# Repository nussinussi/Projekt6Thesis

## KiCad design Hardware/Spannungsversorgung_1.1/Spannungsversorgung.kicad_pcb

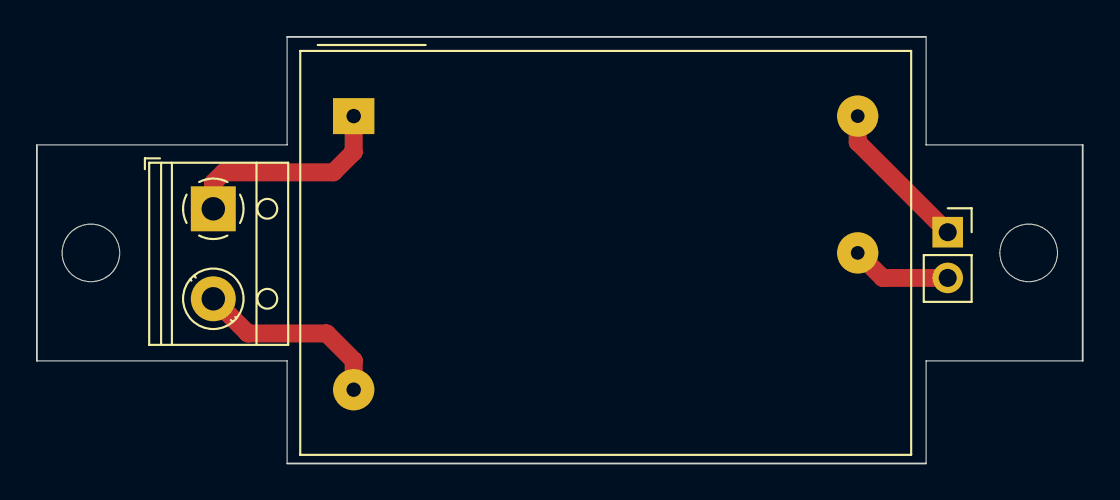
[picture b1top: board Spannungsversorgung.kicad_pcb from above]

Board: 2 copper layers, 58.1 x 23.7 mm, 5 parts (0 on the bottom side), 4 nets.

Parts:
H1, H2: MountingHole; MountingHole_3.2mm_M3_ISO14580
J1: Screw_Terminal_01x02; TerminalBlock_RND_205-00012_1x02_P5.00mm_Horizontal
J2: Conn_01x02_Male; PinSocket_1x02_P2.54mm_Vertical
PS1: IRM-02-5; Converter_ACDC_MeanWell_IRM-02-xx_THT

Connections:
unnamed: J1.1, PS1.1
unnamed: J1.2, PS1.2
unnamed: J2.1, PS1.3
unnamed: J2.2, PS1.4

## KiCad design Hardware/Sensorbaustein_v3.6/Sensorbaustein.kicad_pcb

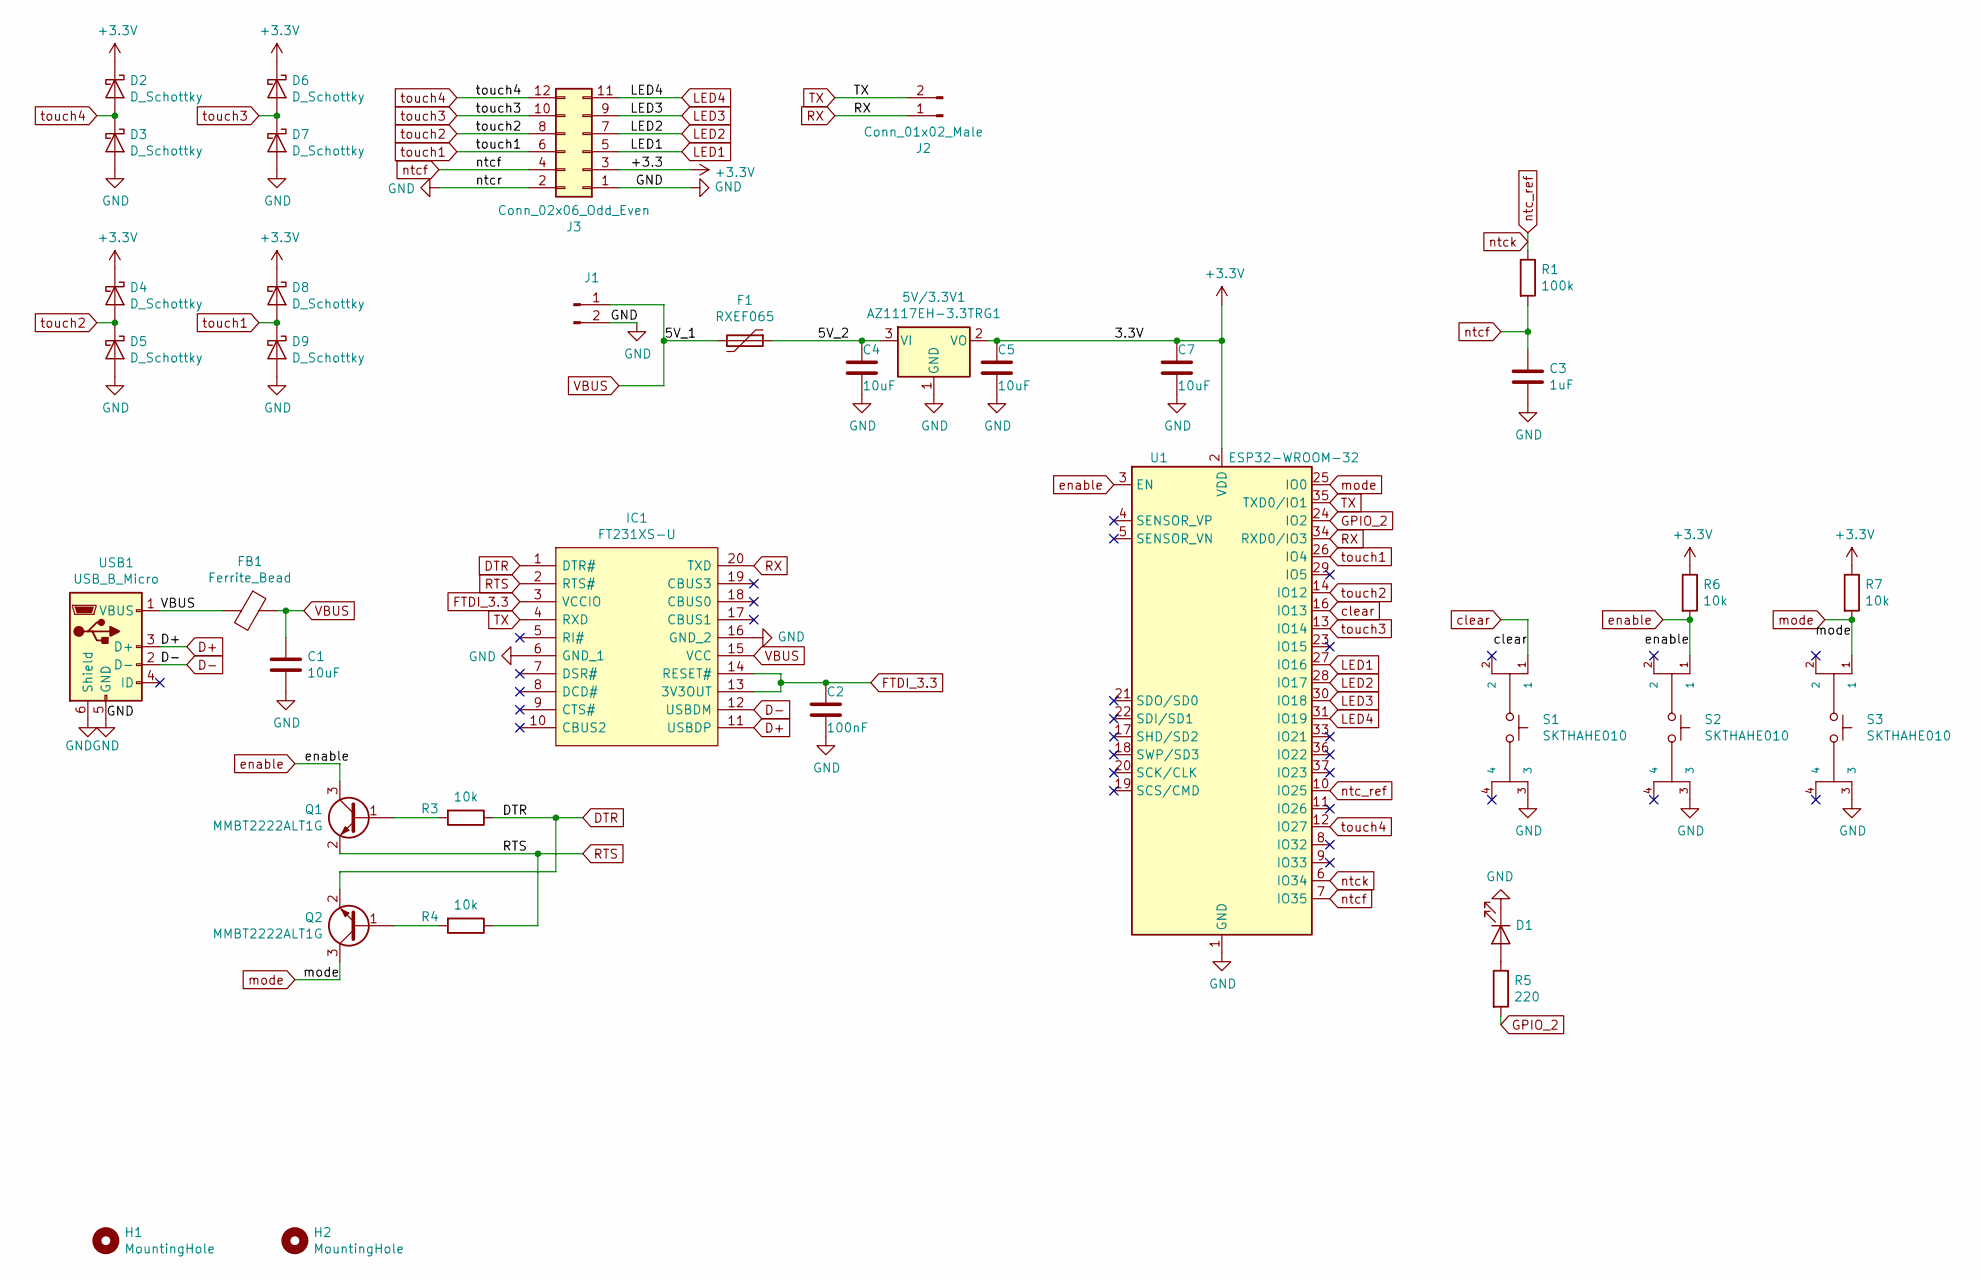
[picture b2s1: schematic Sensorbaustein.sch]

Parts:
5V/3.3V1: AZ1117EH-3.3TRG1; SOT-223-3_TabPin2
C1, C4, C5, C7: 10uF; C_0603_1608Metric_Pad1.05x0.95mm_HandSolder
C2: 100nF; C_0603_1608Metric_Pad1.05x0.95mm_HandSolder
C3: 1uF; C_0603_1608Metric_Pad1.05x0.95mm_HandSolder
D1: 150060BS55040; LED_0603_1608Metric_Pad1.05x0.95mm_HandSolder
D2, D3, D4, D5, D6, D7, D8, D9: D_Schottky; D_SOT-23_ANK
F1: RXEF065; RXEF050
FB1: Ferrite_Bead; R_0603_1608Metric_Pad1.05x0.95mm_HandSolder
H1, H2: MountingHole; MountingHole_3.2mm_M3_ISO14580
IC1: FT231XS-U; SOP64P599X175-20N; Manufacturer_Part_Number FT231XS-U; Mouser Part Number 895-FT231XS-U
J1, J2: Conn_01x02_Male; PinHeader_1x02_P2.54mm_Vertical
J3: Conn_02x06_Odd_Even; PinSocket_2x06_P2.54mm_Vertical
Q1, Q2: MMBT2222ALT1G; SOT-23
R1: 100k; R_0603_1608Metric_Pad1.05x0.95mm_HandSolder
R3, R4, R6, R7: 10k; R_0603_1608Metric_Pad1.05x0.95mm_HandSolder
R5: 220; R_0603_1608Metric_Pad1.05x0.95mm_HandSolder
S1, S2, S3: SKTHAHE010; SW_SKTHAHE010
U1: ESP32-WROOM-32
USB1: USB_B_Micro; USB_Micro-B_Wuerth_629105150521

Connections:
+3V3: 5V/3.3V1.2 (VO), C5.1, C7.1, D2.1 (K), D4.1 (K), D6.1 (K), D8.1 (K), J3.3, R6.1, R7.1, U1.2 (VDD)
/5V_2: 5V/3.3V1.3 (VI), C4.1, F1.1
D+: IC1.11 (USBDP), USB1.3 (D+)
D-: IC1.12 (USBDM), USB1.2 (D-)
DTR: IC1.1 (DTR#), Q2.2 (E), R3.1
FTDI_3.3: C2.1, IC1.3 (VCCIO), IC1.13 (3V3OUT), IC1.14 (RESET#)
GND: 5V/3.3V1.1 (GND), C1.2, C2.2, C3.2, C4.2, C5.2, C7.2, D1.1 (K), D3.2 (A), D5.2 (A), D7.2 (A), D9.2 (A), IC1.6 (GND_1), IC1.16 (GND_2), J1.2, J3.1, J3.2, S1.3, S2.3, S3.3, U1.1 (GND), U1.15 (GND), U1.38 (GND), USB1.5 (GND), USB1.6 (Shield)
GPIO_2: R5.2, U1.24 (IO2)
LED1: J3.5, U1.27 (IO16)
LED2: J3.7, U1.28 (IO17)
LED3: J3.9, U1.30 (IO18)
LED4: J3.11, U1.31 (IO19)
unnamed: D1.2 (A), R5.1
unnamed: Q1.1 (B), R3.2
unnamed: Q2.1 (B), R4.2
RTS: IC1.2 (RTS#), Q1.2 (E), R4.1
RX: IC1.20 (TXD), J2.1, U1.34 (RXD0/IO3)
TX: IC1.4 (RXD), J2.2, U1.35 (TXD0/IO1)
VBUS: C1.1, F1.2, FB1.1, FB1.2, IC1.15 (VCC), J1.1, USB1.1 (VBUS)
clear: S1.1, U1.16 (IO13)
enable: Q1.3 (C), R6.2, S2.1, U1.3 (EN)
mode: Q2.3 (C), R7.2, S3.1, U1.25 (IO0)
ntc_ref: R1.1, U1.6 (IO34), U1.10 (IO25)
ntcf: C3.1, J3.4, R1.2, U1.7 (IO35)
touch1: D8.2 (A), D9.1 (K), J3.6, U1.26 (IO4)
touch2: D4.2 (A), D5.1 (K), J3.8, U1.14 (IO12)
touch3: D6.2 (A), D7.1 (K), J3.10, U1.13 (IO14)
touch4: D2.2 (A), D3.1 (K), J3.12, U1.12 (IO27)

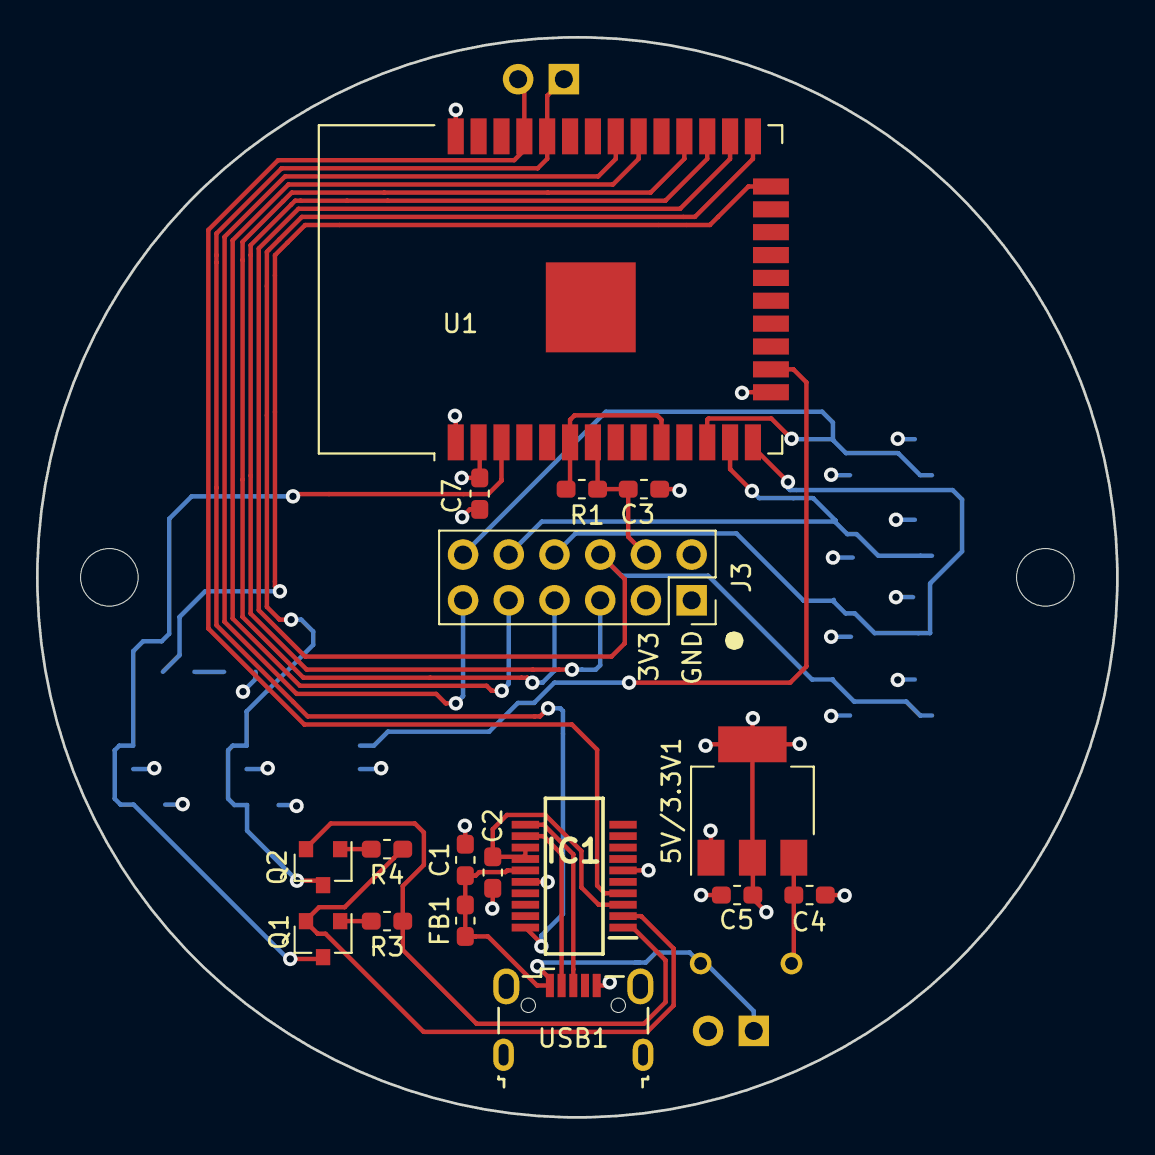
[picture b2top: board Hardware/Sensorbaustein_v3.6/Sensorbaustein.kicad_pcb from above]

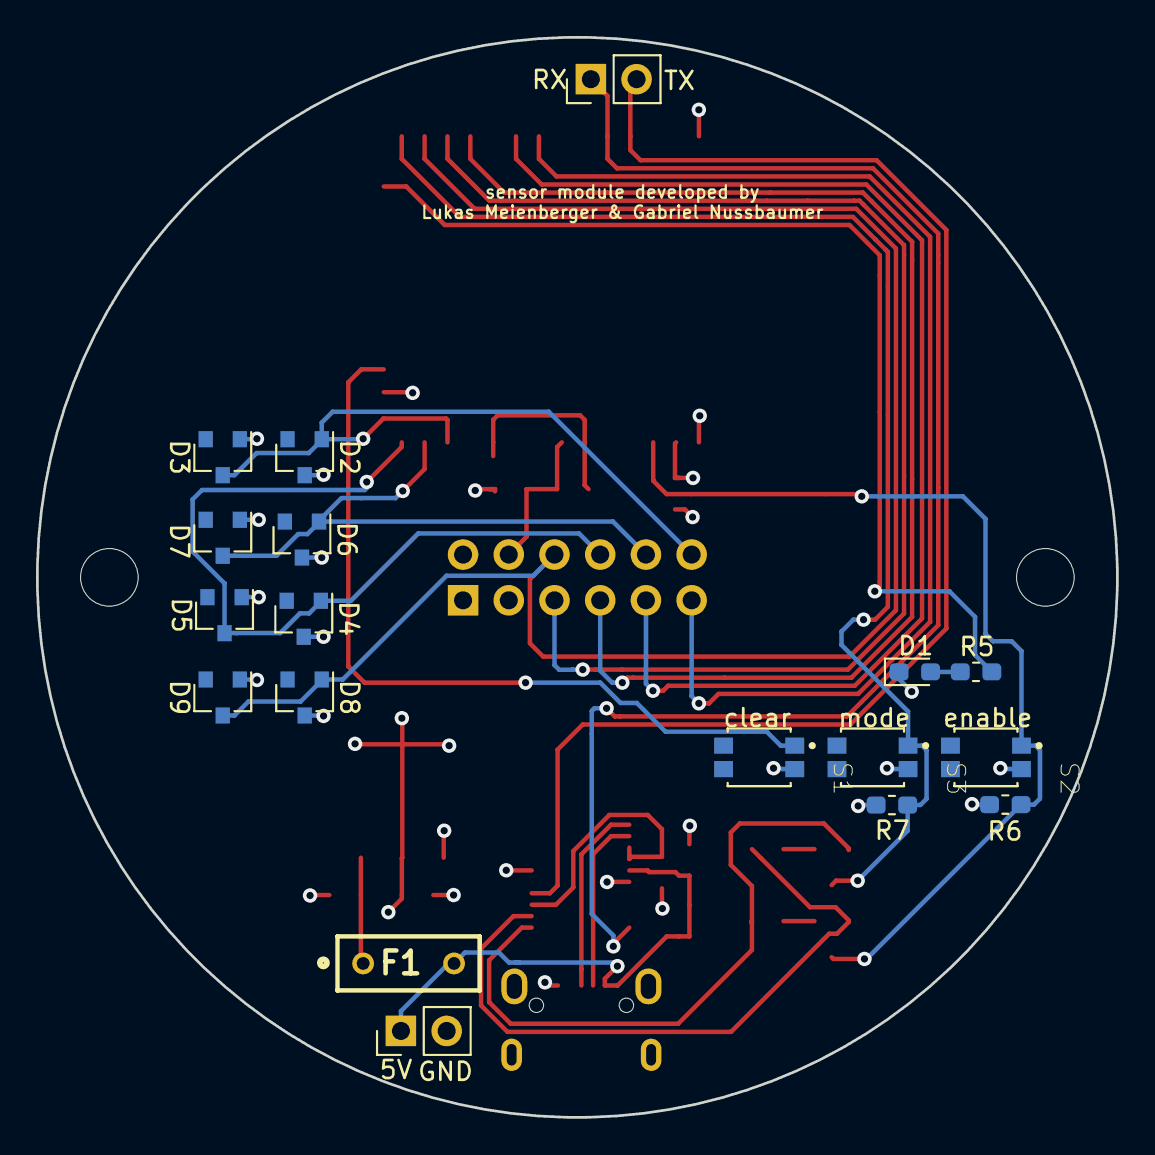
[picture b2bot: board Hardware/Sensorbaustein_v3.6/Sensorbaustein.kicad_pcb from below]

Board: 4 copper layers, 60.0 x 60.0 mm, 37 parts (18 on the bottom side), 28 nets.

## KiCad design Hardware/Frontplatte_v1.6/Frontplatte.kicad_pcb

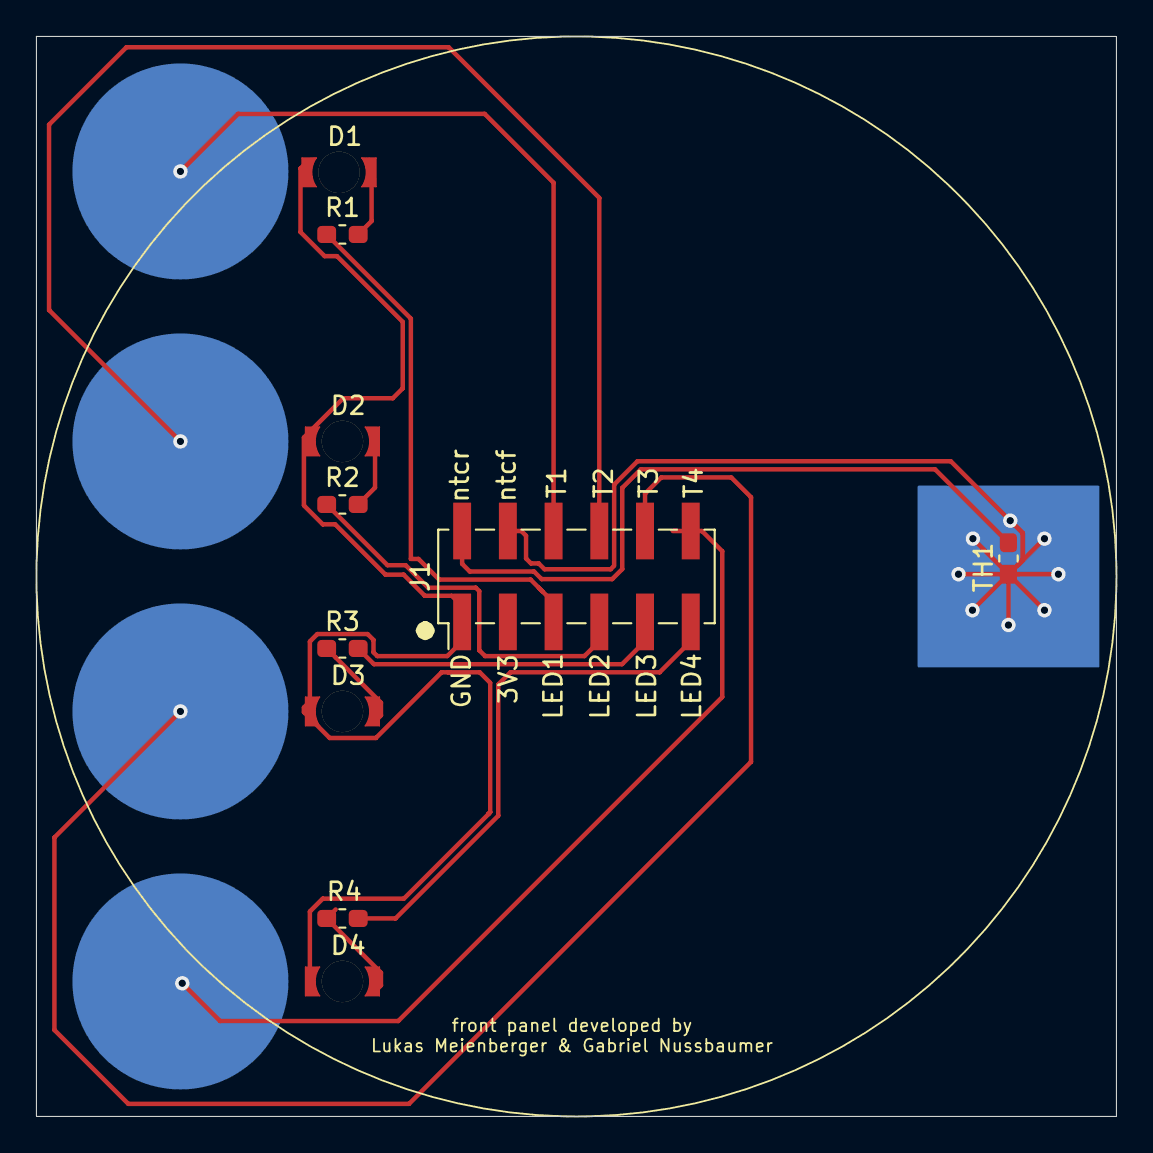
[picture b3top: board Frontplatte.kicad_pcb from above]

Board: 2 copper layers, 60.0 x 60.0 mm, 14 parts (0 on the bottom side), 11 nets.

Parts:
D1, D2, D3, D4: 156120RS75000; reverse_mounted_LED_hole_2.3mm
J1: 61000621121; PinHeader_2x06_P2.54mm_Vertical_SMD
R1, R2, R3, R4: 100; R_0603_1608Metric_Pad1.05x0.95mm_HandSolder
TA1, TA2, TA3, TA4: touch_area_round_12mm; touch_area
TH1: NCU18WF104J60RB; R_0603_1608Metric_Pad1.05x0.95mm_HandSolder

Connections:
GND: D1.1, D2.1, D3.1, D4.1, J1.1
LED1: J1.5, R1.2
LED2: J1.7, R2.2
LED3: J1.9, R3.2
LED4: J1.11, R4.2
unnamed: D1.2, R1.1
unnamed: D2.2, R2.1
unnamed: D3.2, R3.1
unnamed: D4.2, R4.1
ntcf: J1.4, TH1.1
ntcr: J1.2, TH1.2

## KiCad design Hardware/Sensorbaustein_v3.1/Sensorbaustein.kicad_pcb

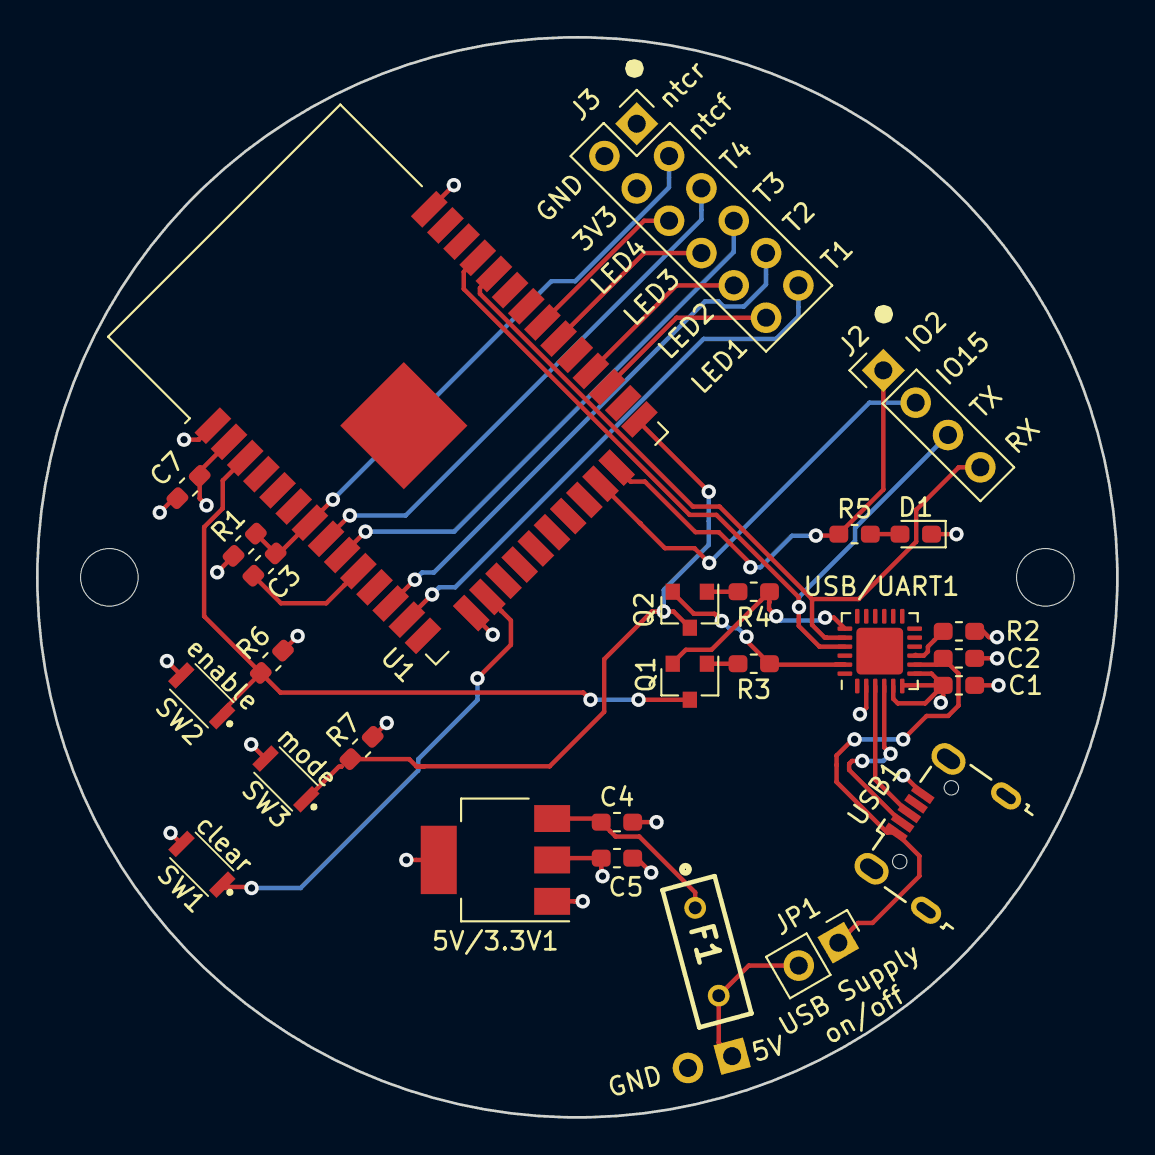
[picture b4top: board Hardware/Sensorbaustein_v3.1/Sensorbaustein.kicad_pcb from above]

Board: 4 copper layers, 60.0 x 60.0 mm, 30 parts (1 on the bottom side), 30 nets.

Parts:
5V/3.3V1: AZ1117EH-3.3TRG1; SOT-223-3_TabPin2
C1: 4.7uF; C_0603_1608Metric_Pad1.05x0.95mm_HandSolder
C2: 100nF; C_0603_1608Metric_Pad1.05x0.95mm_HandSolder
C3: 1uF; C_0603_1608Metric_Pad1.05x0.95mm_HandSolder
C4, C5, C7: 10uF; C_0603_1608Metric_Pad1.05x0.95mm_HandSolder
D1: 150060BS55040; LED_0603_1608Metric_Pad1.05x0.95mm_HandSolder
F1: RXEF065; RXEF050
H1, H2: MountingHole; MountingHole_3.2mm_M3_ISO14580
J1: Conn_01x02_Male; PinHeader_1x02_P2.54mm_Vertical
J2: Conn_01x04_Male; PinHeader_1x04_P2.54mm_Vertical
J3: Conn_02x06_Odd_Even; PinSocket_2x06_P2.54mm_Vertical
JP1: Conn_01x02_Male; PinHeader_1x02_P2.54mm_Vertical
Q1, Q2: MMBT3904; SOT-23
R1: 100k; R_0603_1608Metric_Pad1.05x0.95mm_HandSolder
R2, R3, R4, R6, R7: 10k; R_0603_1608Metric_Pad1.05x0.95mm_HandSolder
R5: 220; R_0603_1608Metric_Pad1.05x0.95mm_HandSolder
SW1, SW2, SW3: TL3780AF100QG; TL3750AF240QG
U1: ESP32-WROOM-32
USB1: USB_B_Micro; USB_Micro-B_Wuerth_629105150521
USB/UART1: CP2104; QFN-24-1EP_4x4mm_P0.5mm_EP2.6x2.6mm

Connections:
+1V1: R1.1, U1.10
+3V3: 5V/3.3V1.2, C1.1, C5.1, C7.1, J3.4, R2.1, R6.1, R7.1, U1.2, USB/UART1.5, USB/UART1.6, USB/UART1.7
/5V_1: F1.2, J1.1, JP1.2
/5V_2: 5V/3.3V1.3, C4.1, F1.1
CHIP_PU: Q1.3, R6.2, SW2.1, U1.3
D+: USB1.3, USB/UART1.3
D-: USB1.2, USB/UART1.4
DTR: Q2.2, R3.1, USB/UART1.23
GND: 5V/3.3V1.1, C1.2, C2.2, C3.2, C4.2, C5.2, C7.2, D1.1, J1.2, J3.1, J3.2, SW1.2, SW2.2, SW3.2, U1.1, U1.15, U1.38, USB1.5, USB1.6, USB/UART1.2
GPIO_0: Q2.3, R7.2, SW3.1, U1.25
GPIO_2: J2.1, R5.2, U1.24
GPIO_15: J2.2, U1.23
LED1: J3.12, U1.27
LED2: J3.10, U1.28
LED3: J3.8, U1.30
LED4: J3.6, U1.31
unnamed: D1.2, R5.1
unnamed: Q1.1, R3.2
unnamed: Q2.1, R4.2
unnamed: R2.2, USB/UART1.9
RTS: Q1.2, R4.1, USB/UART1.19
RXD: J2.4, U1.34, USB/UART1.20
SysReset: SW1.1, U1.16
TXD: J2.3, U1.35, USB/UART1.21
VBUS: C2.1, JP1.1, USB1.1, USB/UART1.8
ntc: C3.1, J3.3, R1.2, U1.7
touch1: J3.11, U1.13
touch2: J3.9, U1.12
touch3: J3.7, U1.9
touch4: J3.5, U1.8

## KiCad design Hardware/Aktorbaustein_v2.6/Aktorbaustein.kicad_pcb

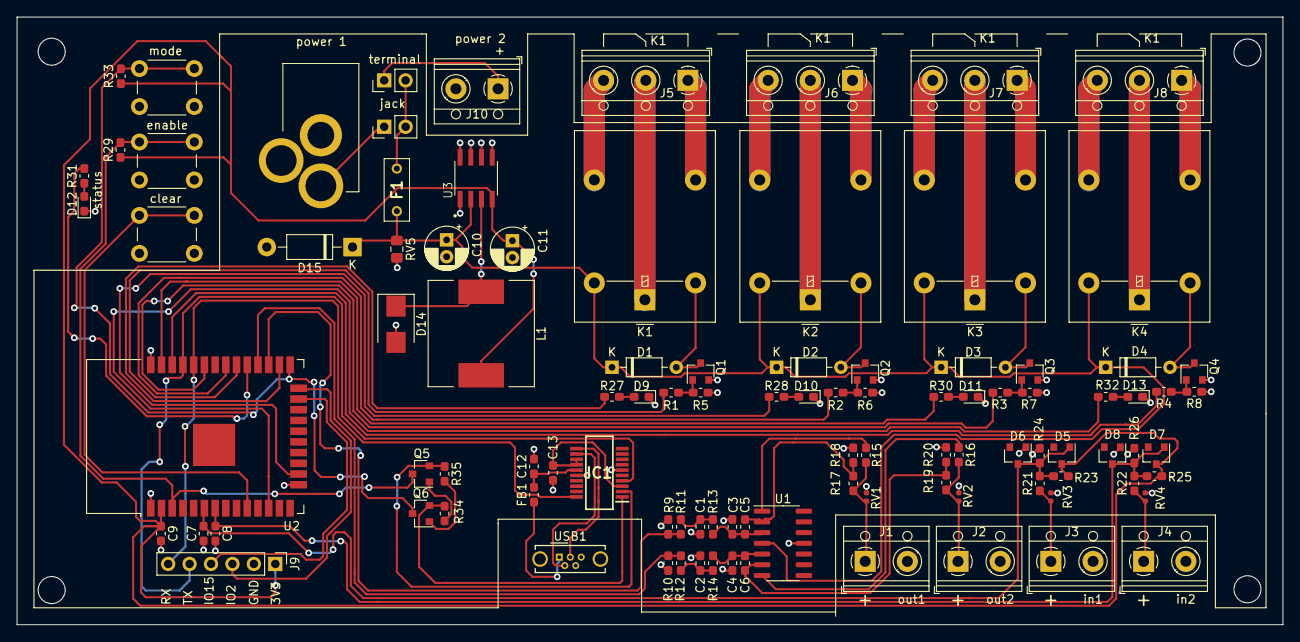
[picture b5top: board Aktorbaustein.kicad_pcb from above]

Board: 2 copper layers, 150.0 x 72.0 mm, 106 parts (0 on the bottom side), 73 nets.

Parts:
C1, C2, C7, C8, C13: 100nF; C_0603_1608Metric_Pad1.05x0.95mm_HandSolder
C3, C4: 10nF; C_0603_1608Metric_Pad1.05x0.95mm_HandSolder
C5, C6: 1nF; C_0603_1608Metric_Pad1.05x0.95mm_HandSolder
C9, C12: 10uF; C_0603_1608Metric_Pad1.05x0.95mm_HandSolder
C10, C11: 15uF; CP_Radial_D5.0mm_P2.00mm
D1, D2, D3, D4: 1N4148; D_DO-35_SOD27_P7.62mm_Horizontal
D5, D6, D7, D8: BAT54; D_SOT-23_ANK
D9, D10, D11, D13: 150060VS55040; LED_0603_1608Metric_Pad1.05x0.95mm_HandSolder
D12: 150060BS55040; LED_0603_1608Metric_Pad1.05x0.95mm_HandSolder
D14: B260; D_SMB
D15: 1N4001G; D_DO-41_SOD81_P10.16mm_Horizontal
F1: RXEF020-AP; RXEF0252
FB1: Ferrite_Bead; R_0603_1608Metric_Pad1.05x0.95mm_HandSolder
H1, H2, H3, H4: MountingHole; MountingHole_3.2mm_M3_ISO7380
IC1: FT231XS-U; SOP64P599X175-20N
J1, J2, J3, J4: TB001-500-02BE; TerminalBlock_RND_205-00012_1x02_P5.00mm_Horizontal
J5, J6, J7, J8: TB002-500-03BE; TerminalBlock_RND_205-00013_1x03_P5.00mm_Horizontal
J9: Conn_01x06_Male; PinHeader_1x06_P2.54mm_Vertical
J10: TB003V-500-P02BE; TerminalBlock_RND_205-00012_1x02_P5.00mm_Horizontal
J11: CON-SOCJ-2155; CONSOCJ2155
JP1, JP2: Jumper; PinHeader_1x02_P2.54mm_Vertical
K1, K2, K3, K4: G5LE-1-VD DC24; Relay_SPDT_Omron-G5LE-1
L1: SRR1260-681K; L_12x12mm_H6mm
Q1, Q2, Q3, Q4: BSS123; SOT-23
Q5, Q6: MMBT3904; SOT-23
R1, R2, R3, R4: 330; R_0603_1608Metric_Pad1.05x0.95mm_HandSolder
R5, R6, R7, R8: 100k; R_0603_1608Metric_Pad1.05x0.95mm_HandSolder
R9, R10, R15, R16, R18, R20, R29, R33, R34, R35: 10k; R_0603_1608Metric_Pad1.05x0.95mm_HandSolder
R11, R12: 3.9k; R_0603_1608Metric_Pad1.05x0.95mm_HandSolder
R13, R14: 39k; R_0603_1608Metric_Pad1.05x0.95mm_HandSolder
R17, R19: 22k; R_0603_1608Metric_Pad1.05x0.95mm_HandSolder
R21, R22: 33k; R_0603_1608Metric_Pad1.05x0.95mm_HandSolder
R23, R25: 120k; R_0603_1608Metric_Pad1.05x0.95mm_HandSolder
R24, R26: 11k; R_0603_1608Metric_Pad1.05x0.95mm_HandSolder
R27, R28, R30, R31, R32: 220; R_0603_1608Metric_Pad1.05x0.95mm_HandSolder
RV1, RV2, RV3, RV4: CG0402MLA-14LG; R_0402_1005Metric
RV5: AVRM2012C330KT801N; R_0805_2012Metric_Pad1.15x1.40mm_HandSolder
SW1, SW2, SW3: SKHHALA010; SW_PUSH_6mm_H4.3mm
U1: LM324A; SOIC-14_3.9x8.7mm_P1.27mm
U2: ESP32-WROOM-32
U3: MIC4680-3.3YM-TR; SOIC127P600X175-8N
USB1: USB_B_Micro; USB_Micro-B_Wuerth_614105150721_Vertical_CircularHoles

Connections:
+3V3: C9.1, C11.1, D5.1, D7.1, J9.1, L1.2, R23.1, R25.1, R29.1, R33.1, U2.2, U3.4
+24V: C10.1, D1.1, D2.1, D3.1, D4.1, D15.1, F1.1, K1.5, K2.5, K3.5, K4.5, RV5.1, U1.4, U3.2
/Logik/24V_F1: F1.2, JP1.2, JP2.2
/Logik/24V_jack: J11.1, JP2.1
/Logik/24V_terminal: J10.1, JP1.1
/Logik/LED1: D9.2, R27.1
/Logik/LED2: D10.2, R28.1
/Logik/LED3: D11.2, R30.1
/Logik/LED4: D13.2, R32.1
/Logik/LED5: D12.2, R31.1
/Logik/VBUS_USB: FB1.1, USB1.1
/Schnittstellen/K1_1: J5.2, K1.1
/Schnittstellen/K1_3: J5.1, K1.3
/Schnittstellen/K1_4: J5.3, K1.4
/Schnittstellen/K2_1: J6.2, K2.1
/Schnittstellen/K2_3: J6.1, K2.3
/Schnittstellen/K2_4: J6.3, K2.4
/Schnittstellen/K3_1: J7.2, K3.1
/Schnittstellen/K3_3: J7.1, K3.3
/Schnittstellen/K3_4: J7.3, K3.4
/Schnittstellen/K4_1: J8.2, K4.1
/Schnittstellen/K4_3: J8.1, K4.3
/Schnittstellen/K4_4: J8.3, K4.4
AD1: C7.1, D5.2, D6.1, R21.2, R23.2, R24.1, U2.6
AD2: C8.1, D7.2, D8.1, R22.2, R25.2, R26.1, U2.7
D+: IC1.11, USB1.3
D-: IC1.12, USB1.2
DTR: IC1.1, Q6.2, R34.1
FTDI_3.3: C13.1, IC1.3, IC1.13, IC1.14
GND: C1.2, C2.2, C3.2, C4.2, C7.2, C8.2, C9.2, C10.2, C11.2, C12.2, C13.2, D6.2, D8.2, D9.1, D10.1, D11.1, D12.1, D13.1, D14.2, D15.2, IC1.6, IC1.16, J1.2, J2.2, J3.2, J4.2, J9.2, J10.2, J11.2, Q1.2, Q2.2, Q3.2, Q4.2, R5.2, R6.2, R7.2, R8.2, R9.2, R10.2, R18.2, R20.2, R24.2, R26.2, RV1.2, RV2.2, RV3.2, RV4.2, RV5.2, SW1.2, SW2.2, SW3.2, U1.11, U2.1, U2.15, U2.38, U3.1, U3.5, U3.6, U3.7, U3.8, USB1.5, USB1.6
GPIO_2: J9.3, U2.24
GPIO_15: J9.4, U2.23
K1: R1.2, U2.30
K2: R2.2, U2.31
K3: R3.2, U2.33
K4: R4.2, U2.36
LED_1: R27.2, U2.26
LED_2: R28.2, U2.16
LED_3: R30.2, U2.37
LED_4: R32.2, U2.12
unnamed: C1.1, R11.1, R13.2
unnamed: C2.1, R12.1, R14.2
unnamed: C3.1, C5.1, R13.1, U1.3
unnamed: C4.1, C6.1, R14.1, U1.5
unnamed: C5.2, R17.2, R18.1, U1.2
unnamed: C6.2, R19.2, R20.1, U1.6
unnamed: D1.2, K1.2, Q1.3
unnamed: D2.2, K2.2, Q2.3
unnamed: D3.2, K3.2, Q3.3
unnamed: D4.2, K4.2, Q4.3
unnamed: D14.1, L1.1, U3.3
unnamed: Q1.1, R1.1, R5.1
unnamed: Q2.1, R2.1, R6.1
unnamed: Q3.1, R3.1, R7.1
unnamed: Q4.1, R4.1, R8.1
unnamed: Q5.1, R34.2
unnamed: Q6.1, R35.2
unnamed: R15.2, U1.1
unnamed: R16.2, U1.7
RTS: IC1.2, Q5.2, R35.1
RXD: IC1.20, J9.6, U2.34
Status: R31.2, U2.29
SysReset: SW1.1, U2.10
TXD: IC1.4, J9.5, U2.35
VBUS: C12.1, FB1.2, IC1.15
enable: Q5.3, R29.2, SW2.1, U2.3
in1: J3.1, R21.1, RV3.1
in2: J4.1, R22.1, RV4.1
mode: Q6.3, R33.2, SW3.1, U2.25
out1: J1.1, R15.1, R17.1, RV1.1
out2: J2.1, R16.1, R19.1, RV2.1
pwm1: R9.1, R11.2, U2.27
pwm2: R10.1, R12.2, U2.28

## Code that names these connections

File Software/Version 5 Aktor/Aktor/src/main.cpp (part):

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#define MQTT_SERIAL_PUBLISH_CH "data/aktorboard/"
#define MQTT_SERIAL_RECEIVER_CH "data/aktorboard/#"
#define R_1 18
#define LED_1 04
#define R_2 19
#define LED_2 13
#define R_3 21
#define LED_3 23
#define R_4 22
#define LED_4 27
#define LED_status 05
#define clear_pin 25 //clear und mode beschriftung vertauscht

char mqtt_server[40];
int mqtt_port = 1883;
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int status = 0;

// the number of the pin
const int out1 = 16; // 16 corresponds to GPIO16
const int out2 = 17; // 16 corresponds to GPIO17
const int AD1 = 34;
const int AD2 = 35;

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float b = -0.34;

// Outputs
int outpins[][2] = {{Channel3, LED_1}, {Channel4, LED_2}, {Channel5, LED_3}, {Channel6, LED_4}};

// Task für 2 Core
TaskHandle_t Task2;
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  ledcSetup(Channel6, freq, resolution); //R4

  // attach the channel to the GPIO to be controlled
  ledcAttachPin(out1, Channel1); // assign chanel to output
  ledcAttachPin(out2, Channel2);
  ledcAttachPin(R_1, Channel3);
  ledcAttachPin(R_2, Channel4);
  ledcAttachPin(R_3, Channel5);
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  Serial.begin(115200);
  pinMode(34, INPUT);
  pinMode(02, INPUT); //Pin I02 test measuring point
  pinMode(clear_pin, INPUT_PULLUP);
  pinMode(LED_status, OUTPUT); //LED-Status
  pinMode(00, INPUT);          //Mode Taster
  for (size_t i = 0; i < 4; i++)
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  wifiManager.addParameter(&custom_mqtt_port);
  wifiManager.addParameter(&custom_board_token);

  if (digitalRead(clear_pin) == 0) //reset 
  {
    wifiManager.startConfigPortal();
  }
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
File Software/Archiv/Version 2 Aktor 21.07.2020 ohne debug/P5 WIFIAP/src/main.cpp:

#include <Arduino.h>
#include <FS.h> //this needs to be first, or it all crashes and burns...
#include <SPIFFS.h>
#include <iostream>
#include <WiFi.h>
#include <esp_wifi.h>
#include <WebServer.h>   //https://github.com/zhouhan0126/WebServer-esp32
#include <DNSServer.h>   //https://github.com/zhouhan0126/DNSServer---esp32
#include <WiFiManager.h> //https://github.com/zhouhan0126/WIFIMANAGER-ESP32
#include "esp_system.h"
#include <Wire.h>
#include <stdio.h>
#include <time.h>
#include <PubSubClient.h>
#include <driver/adc.h>

extern "C"
{
  uint8_t temprature_sens_read();
}

const char *mqtt_server = "192.168.137.6";            //"m16.cloudmqtt.com";
#define mqtt_port 1883                                //12595
#define MQTT_USER "revpi01"                           //"eapcfltj"
#define MQTT_PASSWORD "ganzeasy"                      //"3EjMIy89qzVn"
#define MQTT_SERIAL_PUBLISH_CH "data/aktorboard/1/rx" //"/ESP32/serialdata/FHNW/P5/tx"
#define MQTT_SERIAL_PUBLISH_CH1 "data/aktorboard/1/E1"
#define MQTT_SERIAL_PUBLISH_CH2 "data/aktorboard/1/E2"
#define MQTT_SERIAL_RECEIVER_CH "data/aktorboard/1/#"

WiFiClient wifiClient;
PubSubClient client(wifiClient);

clock_t this_time = clock();
clock_t last_time = this_time;

double tcount = 0;
int NUM_SEC = 10; // Zeit Intervall Messungen
int status = 0;



// the number of the pin
const int out1 = 16; // 16 corresponds to GPIO16
const int out2 = 17; // 16 corresponds to GPIO17
const int AD1 = 34;
const int AD2 = 35;

// setting PWM properties
const int freq = 40000;
const int Channel1 = 0;
const int Channel2 = 1;
const int resolution = 12;
float voltage1 = 0;
float voltage2 = 0;
int duty1 = 0;
int duty2 = 0;

// variable for storing analog input
float in1 = 0;
float in2 = 0;

void setup_wifi()
{

  delay(10);
  while (WiFi.status() != WL_CONNECTED)
  {
    delay(500);
    Serial.print(".");
  }
  randomSeed(micros());
  Serial.println("");
  Serial.println("WiFi connected");
  Serial.println("IP address: ");
  Serial.println(WiFi.localIP());
}
void reconnect()
{
  // Loop until we're reconnected
  while (!client.connected())
  {
    Serial.print("Attempting MQTT connection...");
    // Create a random client ID
    String clientId = "ESP32Client-";
    clientId += String(random(0xffff), HEX);
    // Attempt to connect
    if (client.connect(clientId.c_str(), MQTT_USER, MQTT_PASSWORD))
    {
      Serial.println("connected");
      //Once connected, publish an announcement...
      client.publish("/icircuit/presence/ESP32/", "hello world");
      // ... and resubscribe
      client.subscribe(MQTT_SERIAL_RECEIVER_CH);
    }
    else
    {
      Serial.print("failed, rc=");
      Serial.print(client.state());
      Serial.println(" try again in 5 seconds");
      // Wait 5 seconds before retrying
      delay(5000);
    }
  }
}
void callback(char *topic, byte *payload, unsigned int length)
{


  if (!strncmp((char *)topic, "data/aktorboard/1/K1", 50))
  { //subscribe relais k1-k4
    if (!strncmp((char *)payload, "ON", length))
    {
      digitalWrite(18, HIGH);
      digitalWrite(04, HIGH);
    }
    if (!strncmp((char *)payload, "OFF", length))
    {
      digitalWrite(18, LOW);
      digitalWrite(04, LOW);
    }
  }
  if (!strncmp((char *)topic, "data/aktorboard/1/K2", 50))
  {
    if (!strncmp((char *)payload, "ON", length))
    {
      digitalWrite(19, HIGH);
      digitalWrite(13, HIGH);
    }
    if (!strncmp((char *)payload, "OFF", length))
    {
      digitalWrite(19, LOW);
      digitalWrite(13, LOW);
    }
  }
  if (!strncmp((char *)topic, "data/aktorboard/1/K3", 50))
  {
    if (!strncmp((char *)payload, "ON", length))
    {
      digitalWrite(21, HIGH);
      digitalWrite(23, HIGH);
    }
    if (!strncmp((char *)payload, "OFF", length))
    {
      digitalWrite(21, LOW);
      digitalWrite(23, LOW);
    }
  }
  if (!strncmp((char *)topic, "data/aktorboard/1/K4", 50))
  {
    if (!strncmp((char *)payload, "ON", length))
    {
      digitalWrite(22, HIGH);
      digitalWrite(27, HIGH);
    }
    if (!strncmp((char *)payload, "OFF", length))
    {
      digitalWrite(22, LOW);
      digitalWrite(27, LOW);
    }
  }
  if (!strncmp((char *)topic, "data/aktorboard/1/A1", 50))
  { //Subscribe Analogausgänge
    payload[length] = '\0';
    voltage1 = String((char *)payload).toFloat() * 10;
    duty1 = (voltage1 * 4095) / 10.56;
    ledcWrite(Channel1, duty1);
  }

  if (!strncmp((char *)topic, "data/aktorboard/1/A2", 50))
  {
    payload[length] = '\0';
    voltage2 = String((char *)payload).toFloat() * 10;
    duty2 = (voltage2 * 4095) / 10.56;
    ledcWrite(Channel2, duty2);
  }
}
void publishSerialData(char *serialData)
{
  if (!client.connected())
  {
    reconnect();
  }

  client.publish(MQTT_SERIAL_PUBLISH_CH, serialData);
}

void publishADC()
{
  in1 = (((float(analogRead(AD1) + 218.54)) / 1253.2) - 0.212) / 0.234;
  in2 = (((float(analogRead(AD2) + 218.54)) / 1253.2) - 0.212) / 0.234;
  
  char buffer1[40];
  char buffer2[40];
  sprintf(buffer1, "%.3f", in1);
  sprintf(buffer2, "%.3f", in2);
  if (!client.connected())
  {
    reconnect();
  }
  client.publish(MQTT_SERIAL_PUBLISH_CH1, buffer1);
  client.publish(MQTT_SERIAL_PUBLISH_CH2, buffer2);
}

void setup()
{
  Serial.begin(115200);
  pinMode(34, INPUT);

  pinMode(02, INPUT); //Pin I02 Prüf-Messstelle
  pinMode(04, OUTPUT); //LED1
  pinMode(05, OUTPUT); //LED-Status
  pinMode(13, OUTPUT); //LED2
  pinMode(23, OUTPUT); //LED3
  pinMode(27, OUTPUT); //LED4

  pinMode(18, OUTPUT); //Relais K1
  pinMode(19, OUTPUT); //Relais K2
  pinMode(21, OUTPUT); //Relais K3
  pinMode(22, OUTPUT); //Relais K4

  pinMode(00, INPUT); //Mode Taster
  pinMode(25, INPUT); //Reset Taster

  WiFiManager wifiManager;
  WiFiManagerParameter custom_mqtt_server("Mserver", "mqtt server", "revpi01", 40);
  WiFiManagerParameter custom_mqtt_pw("Mpasswort", "Passwort", "ganzeasy", 40);
  wifiManager.addParameter(&custom_mqtt_server);
  wifiManager.addParameter(&custom_mqtt_pw);

  if (digitalRead(02) == 1) //Sobald reset =1 Fehler auf Layout Theoretisch pin 00 oder 25
  {
    wifiManager.startConfigPortal();
  }
  else
  {
    wifiManager.autoConnect();
  }
  
  client.setServer(mqtt_server, mqtt_port);
  client.setCallback(callback);
  reconnect();

  ledcSetup(Channel1, freq, resolution); //Out PWM 0-10V Konfigurieren
  ledcSetup(Channel2, freq, resolution);

  analogReadResolution(12); //Leg die Auflösung von Analogread auf 12 bits

  ledcAttachPin(out1, Channel1); // chanel dem Output zuweisen
  ledcAttachPin(out2, Channel2);
}

void loop()
{
  client.loop(); // MQTT Client

  this_time = clock();
  tcount += (double)(this_time - last_time);
  last_time = this_time;
  if (tcount > (double)(NUM_SEC * CLOCKS_PER_SEC)) // wird nur alle x Sec durchgeführt
  {
    tcount -= (double)(NUM_SEC * CLOCKS_PER_SEC);
    if (status == 0)
    {
      digitalWrite(05, HIGH); // Status LED blink Modus
      status = 1;
    }
    else
    {
      digitalWrite(05, LOW);
      status = 0;
    }
    publishADC(); //Analogwert Einlesen 0-10V In1 & In2
    
  }
}

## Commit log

2020-04-09 Fachbericht
2020-04-09 ch2
    ch1
2020-04-09 esp code
2020-05-25 software
2020-05-25 Korr Software
2020-05-25 Hardware
2020-06-11 Präsi
2020-06-11 liste
2020-06-11 hfhfhft
2020-06-12 swanp.sensor
2020-06-12 zuzuzu
2020-06-27 Soos
2020-07-09 Software stand 09.07.2020
2020-07-13 bericht
2020-07-13 zgzgzg
2020-07-14 bibliographie
2020-07-14 zgzg
2020-07-15 1123
2020-07-15 ESP aktorboard
2020-08-03 tasks Fachbericht
2020-08-03 Fachbericht Software Sensorboard
2020-08-04 doku sensor software
2020-08-04 doku software sensor
2020-08-05 doku asoftware aktor
2020-08-06 software openhab
2020-08-06 änderungen
2020-08-06 temp
2020-08-06 software openhabian
2020-08-07 Software/Validierung
2020-08-07 Benutzerhandbuch
2020-08-10 Benutzerhanbuch OH
2020-08-10 kompiliert
2020-08-10 energieverbrauch
2020-08-11 bilder
2020-08-11 Benutzerhanbuch Sprachassistant
2020-08-11 Anpassung Software Versionen
2020-08-11 Benutzerhanbuch
2020-08-11 Benutzer HB
2020-08-12 validierung
2020-08-12 Anpassungen Theorie
2020-08-13 zzzuzu
2020-08-13 astract
2020-08-13 Einleitung / Theorie
2020-08-13 Zeitmessung
2020-08-13 server
2020-08-14 verbesserungen
2020-08-14 betriebsanleitung
2020-08-14 schluss
2020-08-14 anhang
2020-08-14 fewafew
2020-08-22 factsheet
2020-08-25 poster
2020-08-25 factsheet, poster
2020-08-25 bildgrösse zip
